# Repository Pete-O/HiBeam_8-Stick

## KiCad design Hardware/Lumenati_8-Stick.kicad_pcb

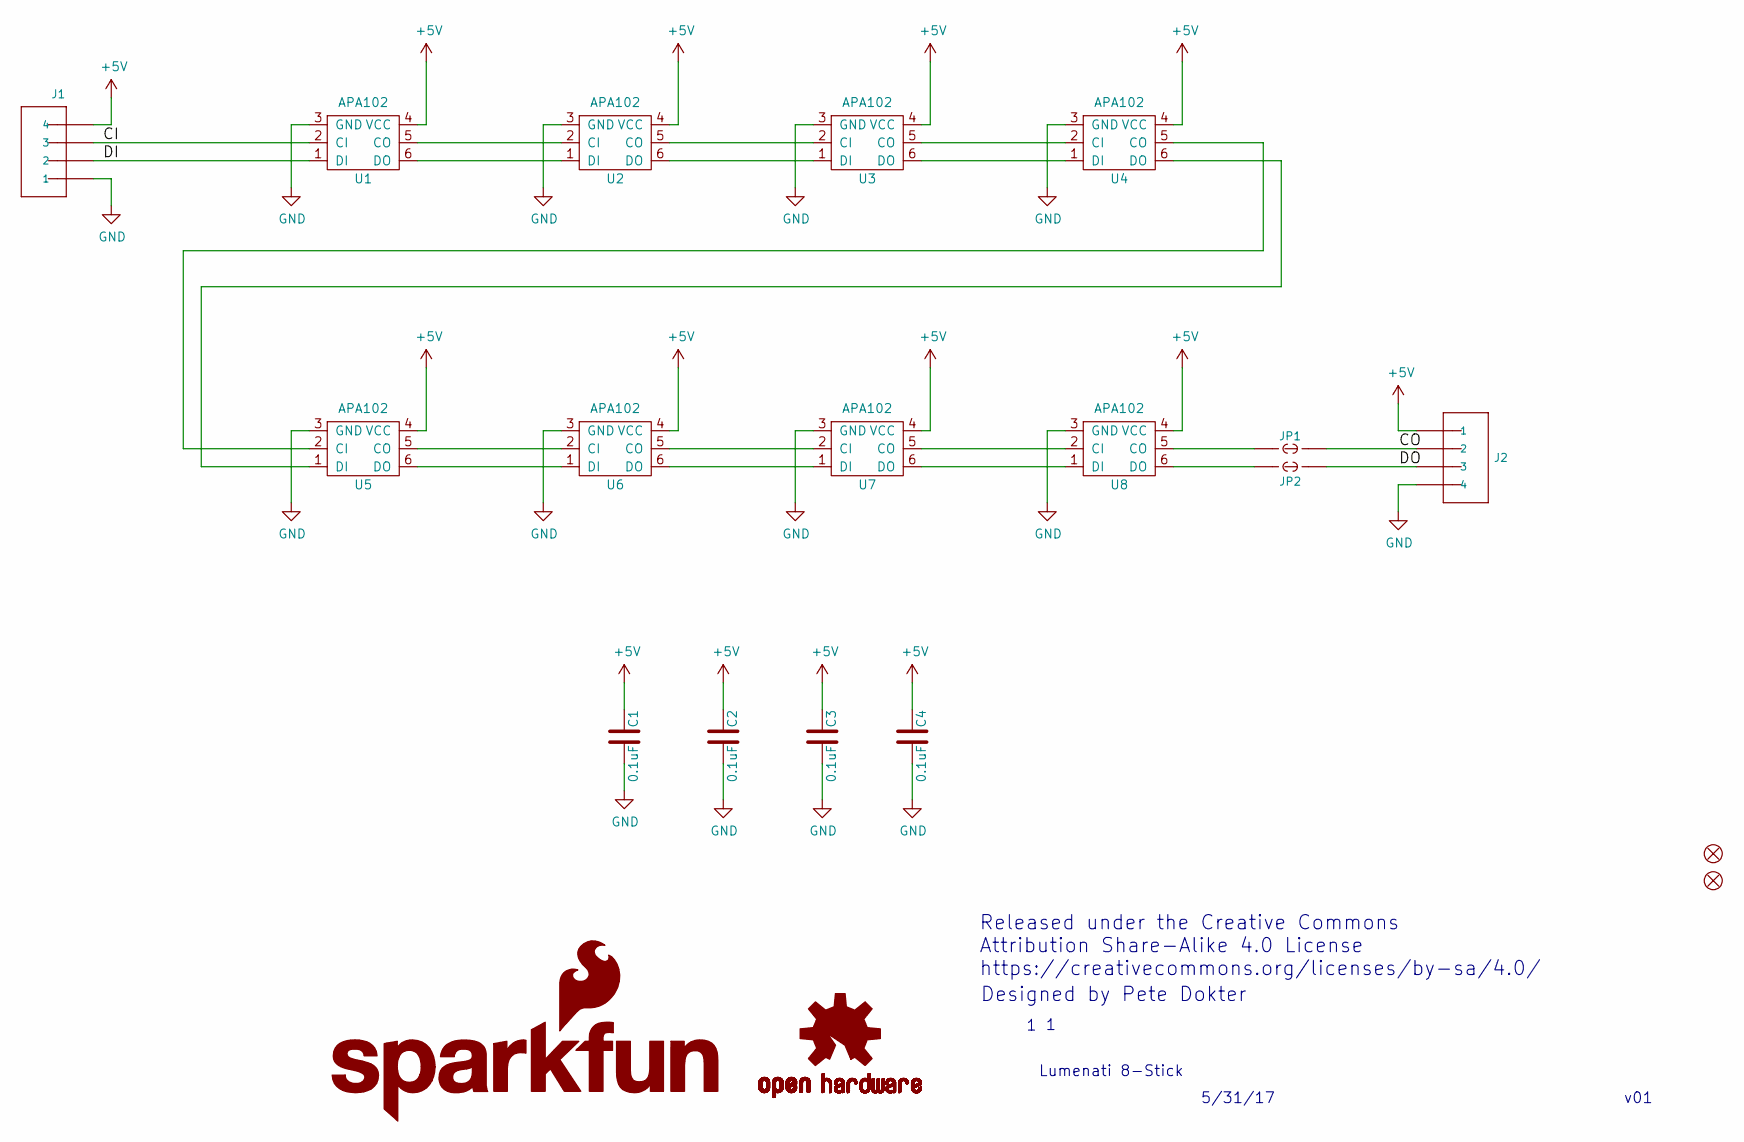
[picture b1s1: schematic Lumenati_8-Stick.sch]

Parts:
C1, C2, C3, C4: 0.1uF; 0603_revised
FD1, FD2: FIDUCIAL1X2
J1, J2: CONN_041X04_NO_SILK; 1X04_NO_SILK
JP1, JP2: JUMPER-SMT_2_NC_TRACE_SILK; SMT-JUMPER_2_NC_TRACE_SILK
LOGO1: SFE_LOGO_NAME_FLAME.1_INCH; SFE_LOGO_NAME_FLAME_.1
LOGO2: OSHW-LOGOMINI; OSHW-LOGO-MINI
U1, U2, U3, U4, U5, U6, U7, U8: APA102; APA102_3

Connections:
+5V: C1.2, C2.2, C3.2, C4.2, J1.4, J2.1, U1.4 (VCC), U2.4 (VCC), U3.4 (VCC), U4.4 (VCC), U5.4 (VCC), U6.4 (VCC), U7.4 (VCC), U8.4 (VCC)
/CI: J1.3, U1.2 (CI)
/CO: J2.2, JP1.2
/DI: J1.2, U1.1 (DI)
/DO: J2.3, JP2.2
GND: C1.1, C2.1, C3.1, C4.1, J1.1, J2.4, U1.3 (GND), U2.3 (GND), U3.3 (GND), U4.3 (GND), U5.3 (GND), U6.3 (GND), U7.3 (GND), U8.3 (GND)
unnamed: JP1.1, U8.5 (CO)
unnamed: JP2.1, U8.6 (DO)
unnamed: U1.5 (CO), U2.2 (CI)
unnamed: U1.6 (DO), U2.1 (DI)
unnamed: U2.5 (CO), U3.2 (CI)
unnamed: U2.6 (DO), U3.1 (DI)
unnamed: U3.5 (CO), U4.2 (CI)
unnamed: U3.6 (DO), U4.1 (DI)
unnamed: U4.5 (CO), U5.2 (CI)
unnamed: U4.6 (DO), U5.1 (DI)
unnamed: U5.5 (CO), U6.2 (CI)
unnamed: U5.6 (DO), U6.1 (DI)
unnamed: U6.5 (CO), U7.2 (CI)
unnamed: U6.6 (DO), U7.1 (DI)
unnamed: U7.5 (CO), U8.2 (CI)
unnamed: U7.6 (DO), U8.1 (DI)

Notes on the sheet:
v01
5/31/17
Lumenati 8-Stick
Released under the Creative Commons Attribution Share-Alike 4.0 License https://creativecommons.org/licenses/by-sa/4.0/
Designed by Pete Dokter

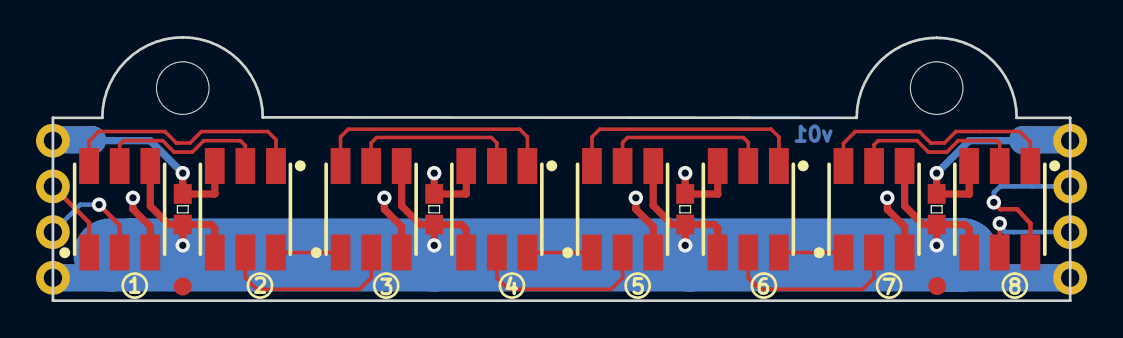
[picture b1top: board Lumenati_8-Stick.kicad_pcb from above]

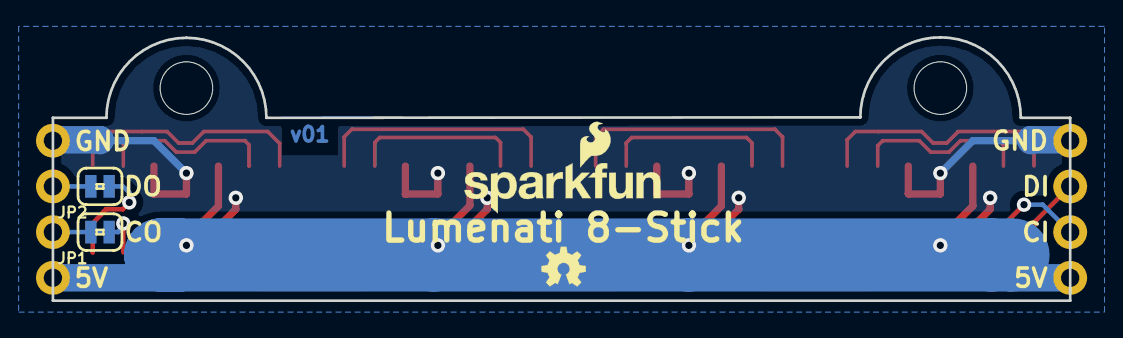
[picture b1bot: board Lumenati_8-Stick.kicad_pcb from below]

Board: 2 copper layers, 56.5 x 14.6 mm, 22 parts (4 on the bottom side), 22 nets.

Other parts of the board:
Ref**: Val**; STAND-OFF_115_2
Ref**#2: Val**; STAND-OFF_115_2

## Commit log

2017-06-08 First commit.
2017-06-09 Fixed silk.
2017-06-13 Castleated connectors.
2017-07-05 Silk fixes.
2017-07-07 Added solder jumpers on the output lines.
2017-08-11 Changed all the names to Lumenati.
2017-08-11 Updated version to v10.
2017-08-18 panel
2017-08-21 Removing paste layer from fiducials on production panel.
2017-08-21 More paste fixes.
2017-10-23 Removing KiCad output files, updating .gitignore.

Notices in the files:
Hardware/Lumenati_8-Stick.kicad_pcb:
https://creativecommons.org/licenses/by-sa/4.0/w
